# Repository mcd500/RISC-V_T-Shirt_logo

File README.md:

# RISC-V T-Shirt logo

Data files for RISC-V Ambassador logos used for creating T-Shirts and notebooks.

The first project used KiCad for designing T-Shirt logos.

The logo data is inspired by PCB layout of the real RISC-V board developed by SparkFun.

The T-Shirt.

## RISC-V Logs in Light Blue and Light Yellows.

## RISC-V Logs in Blue and Yellows.

## RISC-V Logs in Green and Pink.

## RISC-V Logs in Red and Green.

## RISC-V Ambassador logo data

Transparent background.

White background.

# Directory of all data.

## All image files

All image files are located under `images`.

[images](images/)

## Directory of KiCad data files.

The KiCad data was created by converting from original Eagle file format.

The project files and others of KiCad are located under ` SparkFun_REDV_RedBoard-kicad-logo-1`.

Links to the kicad data files.

[kicad](SparkFun_REDV_RedBoard-kicad-logo-1)

## Link to the SparkFun RED-V RedBoard.

https://www.sparkfun.com/products/15594

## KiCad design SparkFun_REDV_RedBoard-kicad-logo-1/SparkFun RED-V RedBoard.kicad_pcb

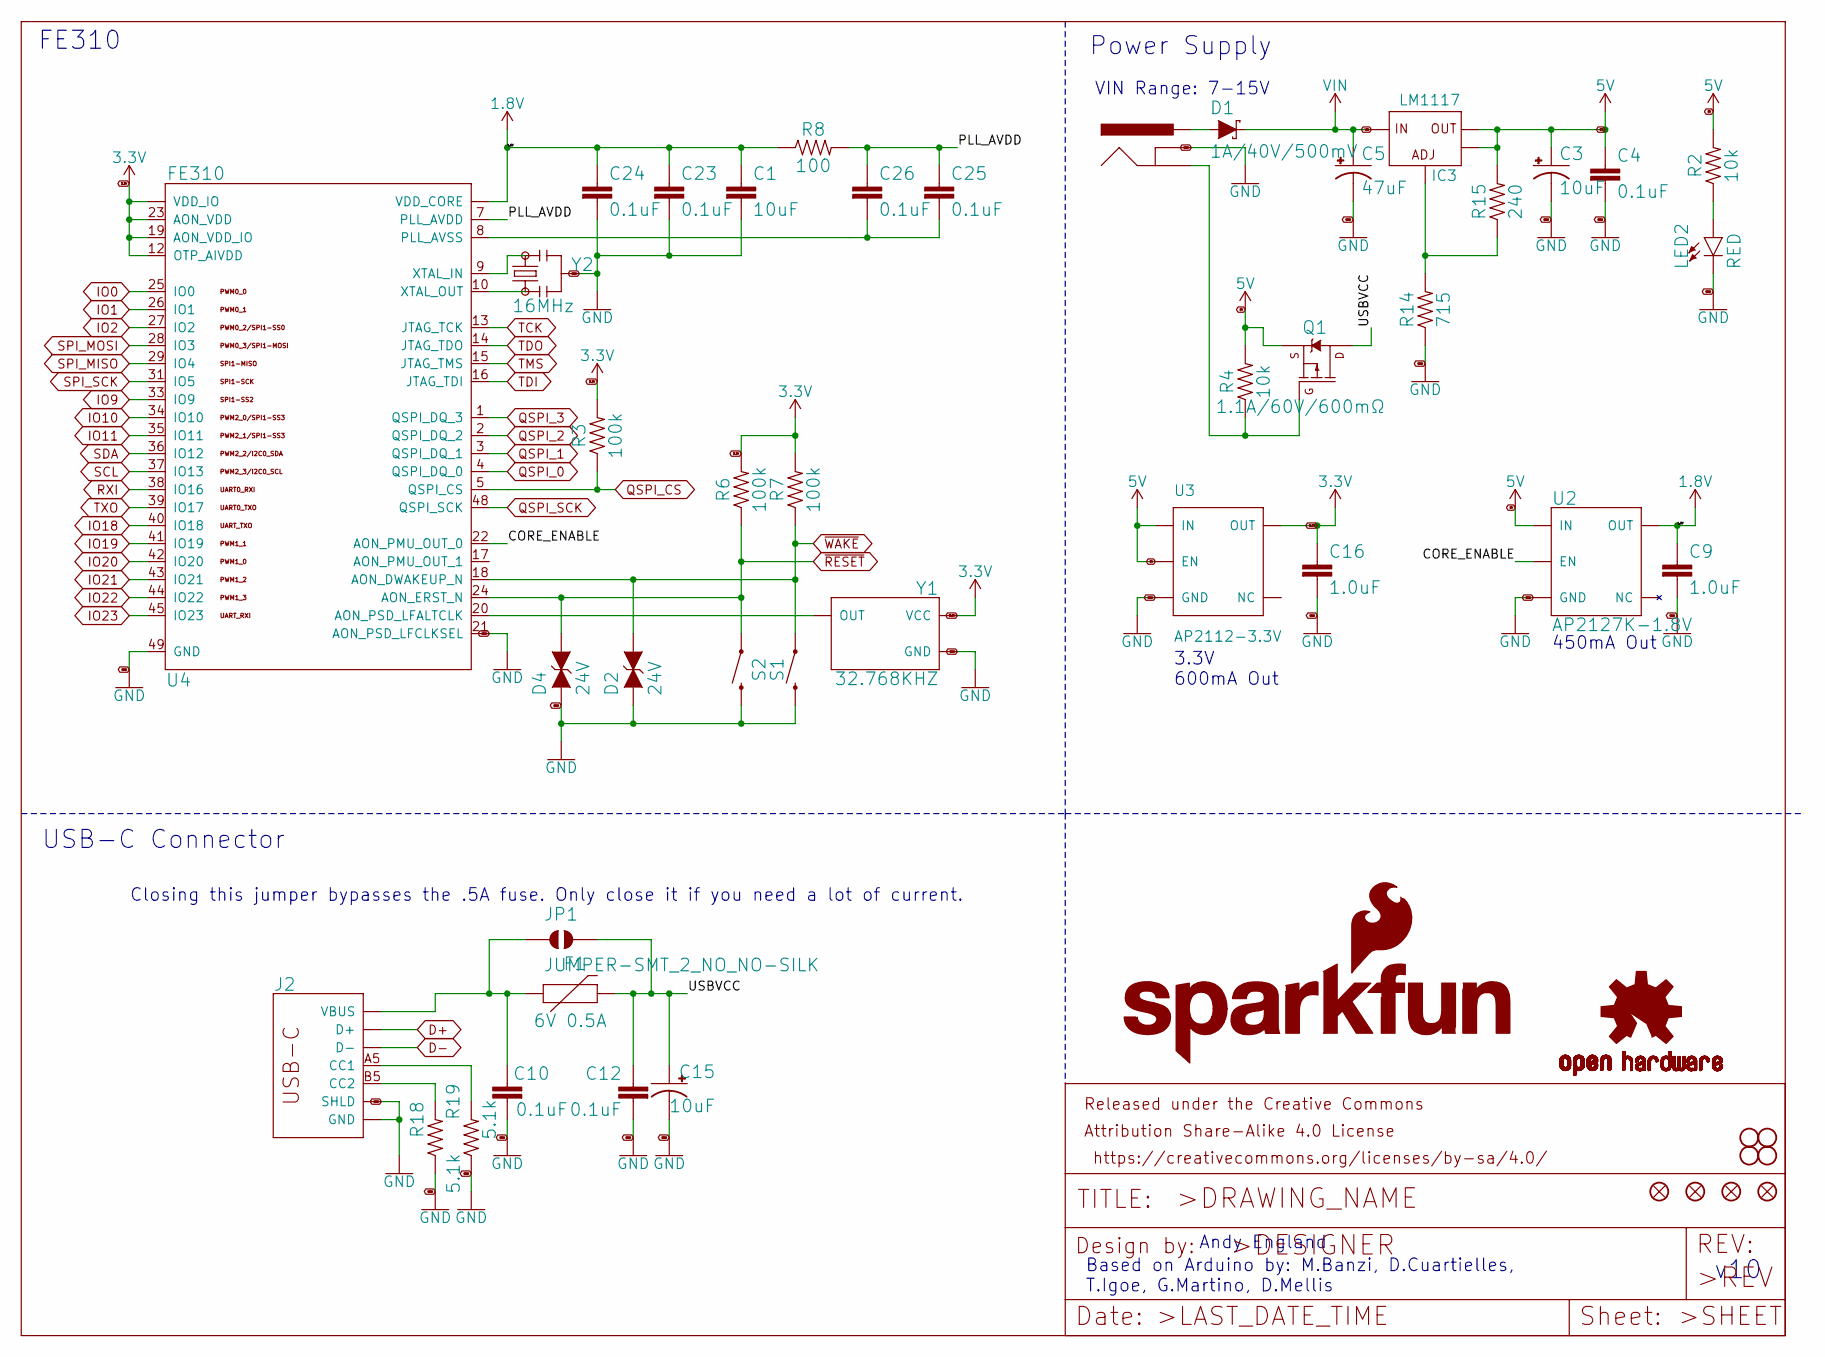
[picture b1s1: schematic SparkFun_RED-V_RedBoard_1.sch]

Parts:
C1: 10uF; 0603
C3, C15: 10uF; EIA3216
C4, C10, C12, C23, C24, C25, C26: 0.1uF; 0603
C5: 47uF; PANASONIC_D
C9, C16: 1.0uF; 0603
D1: 1A/40V/500mV; SMA-DIODE
D2, D4: 24V; 0603
F1: 6V 0.5A; 0805
FRAME2: FRAME-LETTER; CREATIVE_COMMONS
IC3: LM1117; SOT223-ALT1
J2: USB Female Type C Connector; USB-C-16P
J3: POWER_JACKSUPER_BOMB_DIGITY; POWER_JACK_SMD_OVERPASTE_SUPER_BOMB_DIGITY
JP1: JUMPER-SMT_2_NO_NO-SILK; SMT-JUMPER_2_NO_NO-SILK
JP3, JP4, JP5, JP6: STAND-OFF
JP8, JP9, JP15, JP16: FIDUCIAL1X2; FIDUCIAL-1X2
LED2: RED; LED-1206
LOGO1: SFE_LOGO_NAME_FLAME.1_INCH; SFE_LOGO_NAME_FLAME_.1
Q1: 1.1A/60V/600mΩ; SOT23-3
R2, R4: 10k; 0603
R3, R6, R7: 100k; 0603
R8: 100; 0603
R14: 715; 0603
R15: 240; 0603
R18, R19: 5.1k; 0603
S1, S2: MOMENTARY-SWITCH-SPST-SMD-6.2MM-TALL; TACTILE_SWITCH_SMD_6.2MM_TALL
U2: AP2127K-1.8V; SOT23-5
U3: AP2112-3.3V; SOT23-5
U4: FE310; QFN-48-.4MMPITCH
U$16: OSHW-LOGOS; OSHW-LOGO-S
Y1: 32.768KHZ; CRYSTAL-SMD-2X1.2MM
Y2: 16MHz; RESONATOR-SMD-3.2X1.3

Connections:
1.8V: C1.1, C9.1, C23.1, C24.1, R8.1, U2.5 (OUT), U4.6 (VDD_CORE), U4.30 (VDD_CORE), U4.46 (VDD_CORE)
3.3V: C16.1, R3.2, R6.2, R7.2, U3.5 (OUT), U4.11 (VDD_IO), U4.12 (OTP_AIVDD), U4.19 (AON_VDD_IO), U4.23 (AON_VDD), U4.32 (VDD_IO), U4.47 (VDD_IO), Y1.4 (VCC); also elsewhere on the board
5V: C3.+, C4.1, IC3.2 (OUT), IC3.4 (OUT@1), Q1.2 (S), R2.2, R4.2, R15.2, U2.1 (IN), U3.1 (IN), U3.3 (EN); also elsewhere on the board
/SparkFun RED-V RedBoard_1/CORE_ENABLE: U2.3 (EN), U4.22 (AON_PMU_OUT_0)
/SparkFun RED-V RedBoard_1/PLL_AVDD: C25.1, C26.1, R8.2, U4.7 (PLL_AVDD)
/SparkFun RED-V RedBoard_1/USBVCC: C12.1, C15.+, F1.2, JP1.2, Q1.3 (D)
D+: J2.A6 (D+), J2.B6 (D+); also elsewhere on the board
D-: J2.A7 (D-), J2.B7 (D-); also elsewhere on the board
GND: C1.2, C3.-, C4.2, C5.-, C9.2, C10.2, C12.2, C15.-, C16.2, C23.2, C24.2, D2.1 (A), D4.1 (A), J2.GND, J2.GND2 (GND), J2.SHLD1 (SHLD), J2.SHLD2 (SHLD), J2.SHLD3 (SHLD), J2.SHLD4 (SHLD), J2.SHLD5 (SHLD), J2.SHLD6 (SHLD), J2.SHLD7 (SHLD), J2.SHLD8 (SHLD), J3.GND (GNDBREAK), LED2.C, R14.1, R18.1, R19.1, S1.B2 (2), S2.B2 (2), U2.2 (GND), U3.2 (GND), U4.21 (AON_PSD_LFCLKSEL), U4.49 (GND), Y1.2 (GND), Y2.2; also elsewhere on the board
IO0: U4.25 (IO0); also elsewhere on the board
IO1: U4.26 (IO1); also elsewhere on the board
IO2: U4.27 (IO2); also elsewhere on the board
IO9: U4.33 (IO9); also elsewhere on the board
IO10: U4.34 (IO10); also elsewhere on the board
IO11: U4.35 (IO11); also elsewhere on the board
IO18: U4.40 (IO18); also elsewhere on the board
IO19: U4.41 (IO19); also elsewhere on the board
IO20: U4.42 (IO20); also elsewhere on the board
IO21: U4.43 (IO21); also elsewhere on the board
IO22: U4.44 (IO22); also elsewhere on the board
IO23: U4.45 (IO23); also elsewhere on the board
unnamed: C10.1, F1.1, J2.VBUS1 (VBUS), J2.VBUS2 (VBUS), JP1.1
unnamed: C25.2, C26.2, U4.8 (PLL_AVSS)
unnamed: D1.A, J3.VIN0 (PWR)
unnamed: IC3.1 (ADJ), R14.2, R15.1
unnamed: J2.A5 (CC1), R19.2
unnamed: J2.B5 (CC2), R18.2
unnamed: J3.P$4 (GND), Q1.1 (G), R4.1
unnamed: LED2.A, R2.1
unnamed: U4.9 (XTAL_IN), Y2.3
unnamed: U4.10 (XTAL_OUT), Y2.1
unnamed: U4.20 (AON_PSD_LFALTCLK), Y1.3 (OUT)
QSPI_0: U4.4 (QSPI_DQ_0); also elsewhere on the board
QSPI_1: U4.3 (QSPI_DQ_1); also elsewhere on the board
QSPI_2: U4.2 (QSPI_DQ_2); also elsewhere on the board
QSPI_3: U4.1 (QSPI_DQ_3); also elsewhere on the board
QSPI_CS: R3.1, U4.5 (QSPI_CS); also elsewhere on the board
QSPI_SCK: U4.48 (QSPI_SCK); also elsewhere on the board
RXI: U4.38 (IO16); also elsewhere on the board
SCL: U4.37 (IO13); also elsewhere on the board
SDA: U4.36 (IO12); also elsewhere on the board
SPI_MISO: U4.29 (IO4); also elsewhere on the board
SPI_MOSI: U4.28 (IO3); also elsewhere on the board
SPI_SCK: U4.31 (IO5); also elsewhere on the board
TCK: U4.13 (JTAG_TCK); also elsewhere on the board
TDI: U4.16 (JTAG_TDI); also elsewhere on the board
TDO: U4.14 (JTAG_TDO); also elsewhere on the board
TMS: U4.15 (JTAG_TMS); also elsewhere on the board
TXO: U4.39 (IO17); also elsewhere on the board
VIN: C5.+, D1.C, IC3.3 (IN); also elsewhere on the board
~RESET: D4.2 (C), R6.1, S2.A2 (1), U4.24 (AON_ERST_N); also elsewhere on the board
~WAKE: D2.2 (C), R7.1, S1.A2 (1), U4.18 (AON_DWAKEUP_N); also elsewhere on the board

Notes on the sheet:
Power Supply
FE310
USB-C Connector
Based on Arduino by: M.Banzi, D.Cuartielles, T.Igoe, G.Martino, D.Mellis
Andy England
v10
VIN Range: 7-15V
3.3V 600mA Out
450mA Out
Closing this jumper bypasses the .5A fuse. Only close it if you need a lot of current.

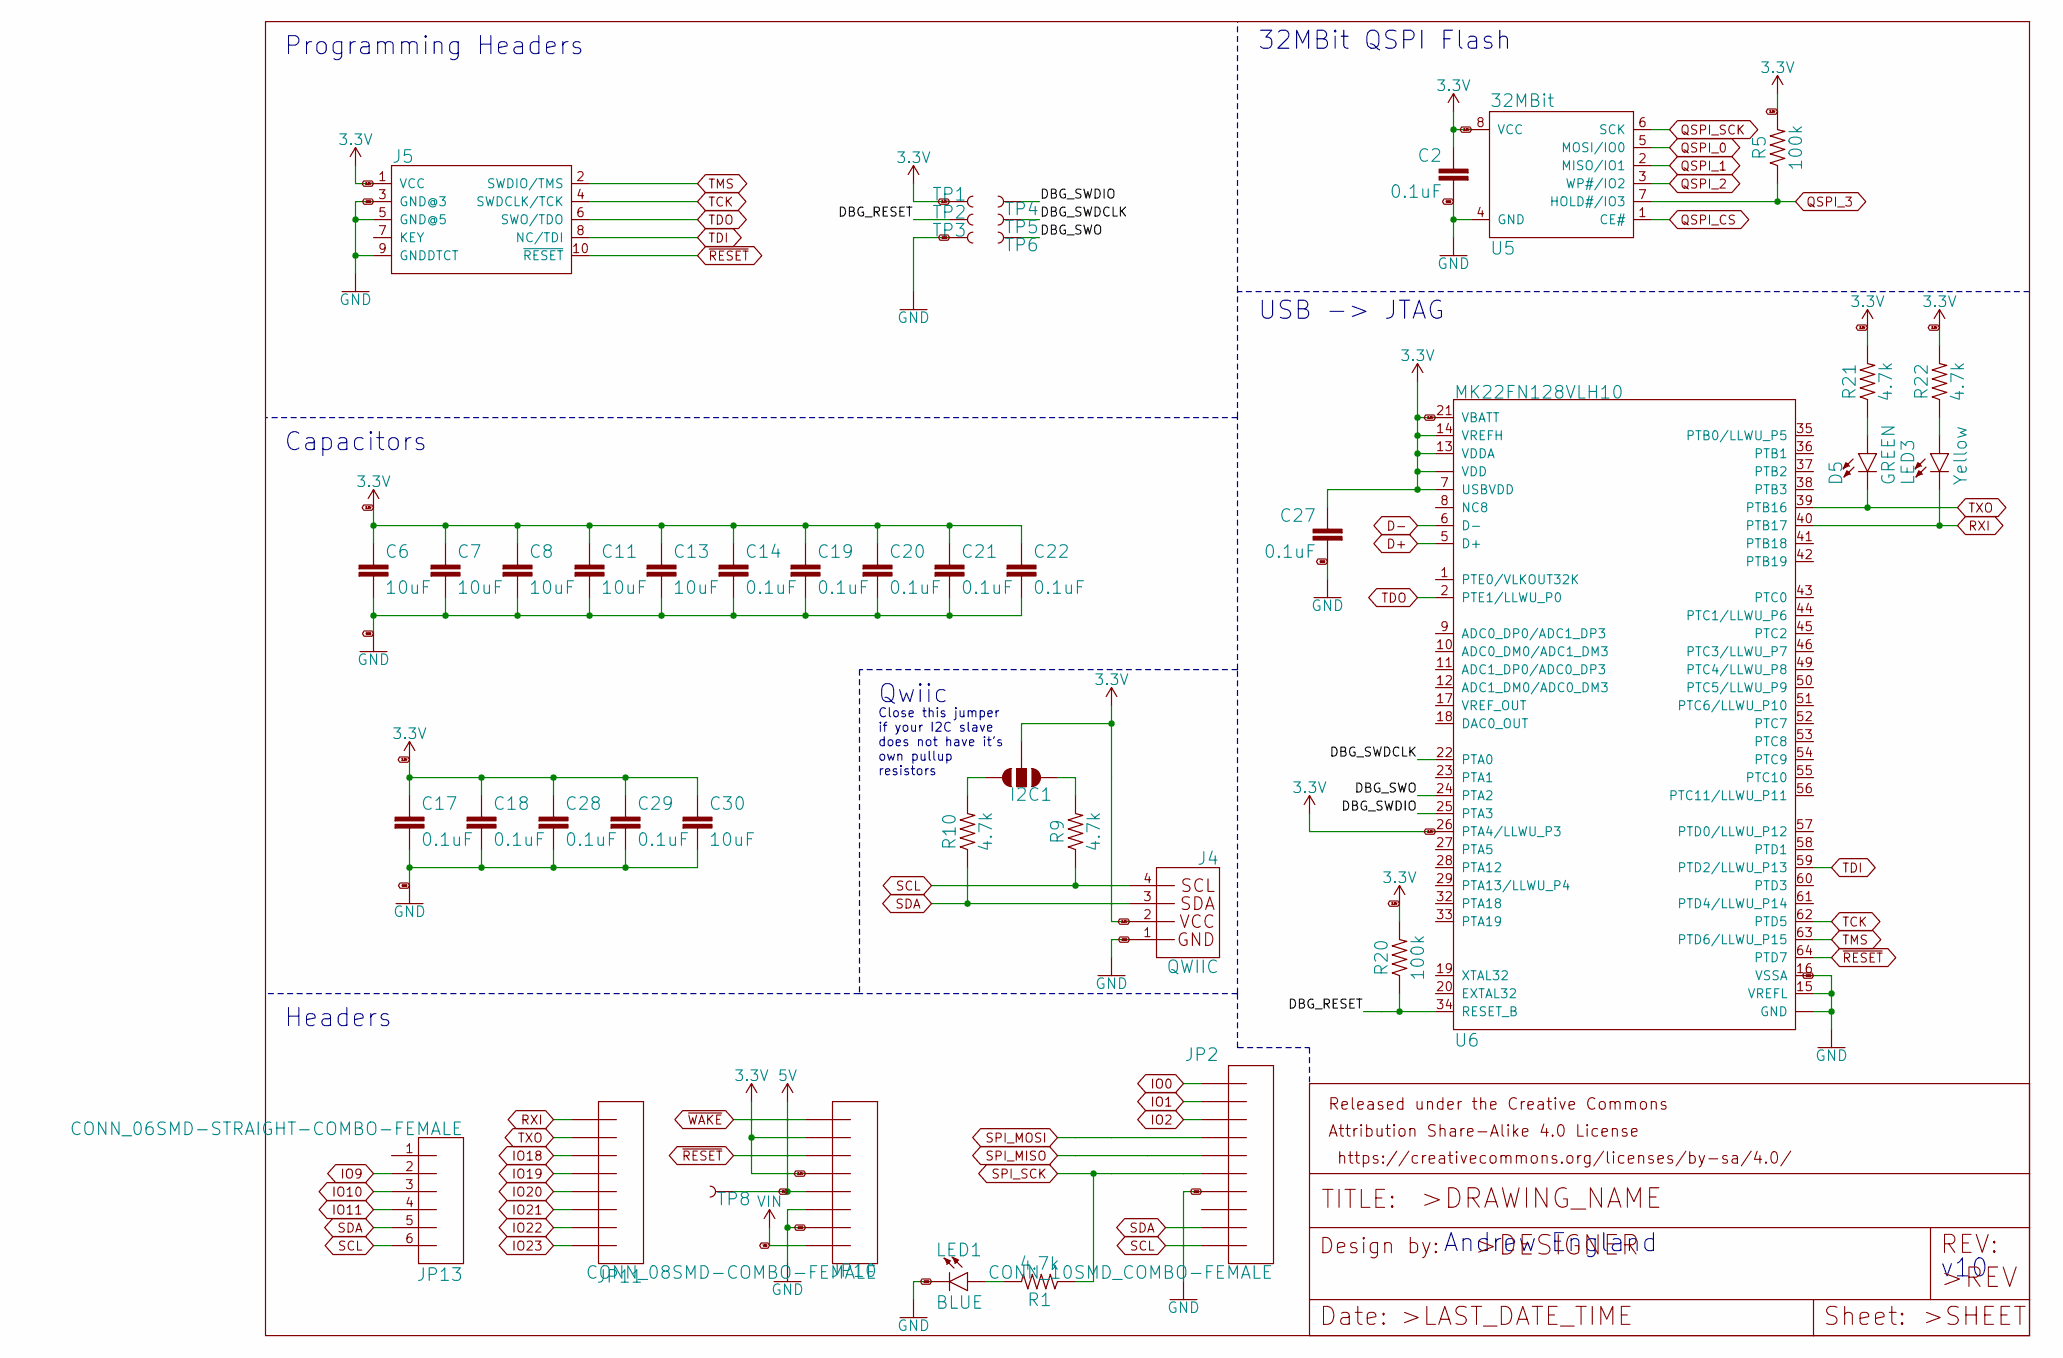
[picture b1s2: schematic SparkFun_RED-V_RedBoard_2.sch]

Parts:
C2, C14, C17, C18, C19, C20, C21, C22, C27, C28, C29: 0.1uF; 0603
C6, C7, C8, C11, C13, C30: 10uF; 0603
D5: GREEN; LED-1206
FRAME1: FRAME-LETTER; CREATIVE_COMMONS
I2C: JUMPER-SMT_3_NO_NO-SILK; SMT-JUMPER_3_NO_NO-SILK
J4: QWIIC; JST04_1MM_RA
J5: CORTEX_JTAG_DEBUG_PTH_NS; 2X5-PTH-1.27MM-NO_SILK
JP2: CONN_10SMD_COMBO-FEMALE; 1X10_SMD_COMBINED
JP10: CONN_08SMD-COMBO-FEMALE; 1X08_SMD_COMBINED
JP11: JP11; 1X08_SMD_COMBINED
JP13: CONN_06SMD-STRAIGHT-COMBO-FEMALE; 1X06_SMD_STRAIGHT_COMBO
LED1: BLUE; LED-1206
LED3: Yellow; LED-1206
R1, R9, R10, R21, R22: 4.7k; 0603
R5, R20: 100k; 0603
TP1, TP2, TP3, TP4, TP5, TP6: TEST-POINT3X5; PAD.03X.05
TP8: TEST-POINT3; PAD.03X.03
U5: 32MBit; SO08
U6: MK22FN128VLH10; LQFP-64

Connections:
3.3V: C2.1, C6.1, C7.1, C8.1, C11.1, C13.1, C14.1, C17.1, C18.1, C19.1, C20.1, C21.1, C22.1, C27.1, C28.1, C29.1, C30.1, J4.2, J5.1 (VCC), JP10.5, JP10.5@2 (5), JP10.7, JP10.7@2 (7), R5.2, R20.2, R21.2, R22.2, TP1.P$1, U5.8 (VCC), U6.3 (VDD), U6.7 (USBVDD), U6.13 (VDDA), U6.14 (VREFH), U6.21 (VBATT), U6.26 (PTA4/LLWU_P3), U6.30 (VDD), U6.48 (VDD); also elsewhere on the board
5V: JP10.4, JP10.4@2 (4), TP8.P$1; also elsewhere on the board
/SparkFun RED-V RedBoard_2/DBG_RESET: R20.1, TP2.P$1, U6.34 (RESET_B)
/SparkFun RED-V RedBoard_2/DBG_SWDCLK: TP5.P$1, U6.22 (PTA0)
/SparkFun RED-V RedBoard_2/DBG_SWDIO: TP4.P$1, U6.25 (PTA3)
/SparkFun RED-V RedBoard_2/DBG_SWO: TP6.P$1, U6.24 (PTA2)
D+: U6.5 (D+); also elsewhere on the board
D-: U6.6 (D-); also elsewhere on the board
GND: C2.2, C6.2, C7.2, C8.2, C11.2, C13.2, C14.2, C17.2, C18.2, C19.2, C20.2, C21.2, C22.2, C27.2, C28.2, C29.2, C30.2, J4.1, J5.3 (GND@3), J5.5 (GND@5), J5.9 (GNDDTCT), JP2.4A (4), JP2.4B (4), JP10.2, JP10.2@2 (2), JP10.3, JP10.3@2 (3), LED1.C, TP3.P$1, U5.4 (GND), U6.4 (GND), U6.15 (VREFL), U6.16 (VSSA), U6.31 (GND), U6.47 (GND); also elsewhere on the board
IO0: JP2.10A (10), JP2.10B (10); also elsewhere on the board
IO1: JP2.9A (9), JP2.9B (9); also elsewhere on the board
IO2: JP2.8A (8), JP2.8B (8); also elsewhere on the board
IO9: JP13.2; also elsewhere on the board
IO10: JP13.3; also elsewhere on the board
IO11: JP13.4; also elsewhere on the board
IO18: JP11.3, JP11.3@2 (3); also elsewhere on the board
IO19: JP11.4, JP11.4@2 (4); also elsewhere on the board
IO20: JP11.5, JP11.5@2 (5); also elsewhere on the board
IO21: JP11.6, JP11.6@2 (6); also elsewhere on the board
IO22: JP11.7, JP11.7@2 (7); also elsewhere on the board
IO23: JP11.8, JP11.8@2 (8); also elsewhere on the board
unnamed: D5.A, R21.1
unnamed 29: R9.2; also elsewhere on the board
unnamed 30: R10.2; also elsewhere on the board
unnamed: JP2.3A (3), JP2.3B (3)
unnamed: LED1.A, R1.2
unnamed: LED3.A, R22.1
QSPI_0: U5.5 (MOSI/IO0); also elsewhere on the board
QSPI_1: U5.2 (MISO/IO1); also elsewhere on the board
QSPI_2: U5.3 (WP#/IO2); also elsewhere on the board
QSPI_3: R5.1, U5.7 (HOLD#/IO3); also elsewhere on the board
QSPI_CS: U5.1 (CE#); also elsewhere on the board
QSPI_SCK: U5.6 (SCK); also elsewhere on the board
RXI: JP11.1, JP11.1@2 (1), LED3.C, U6.40 (PTB17); also elsewhere on the board
SCL: J4.4, JP2.1A (1), JP2.1B (1), JP13.6, R9.1; also elsewhere on the board
SDA: J4.3, JP2.2A (2), JP2.2B (2), JP13.5, R10.1; also elsewhere on the board
SPI_MISO: JP2.6A (6), JP2.6B (6); also elsewhere on the board
SPI_MOSI: JP2.7A (7), JP2.7B (7); also elsewhere on the board
SPI_SCK: JP2.5A (5), JP2.5B (5), R1.1; also elsewhere on the board
TCK: J5.4 (SWDCLK/TCK), U6.62 (PTD5); also elsewhere on the board
TDI: J5.8 (NC/TDI), U6.59 (PTD2/LLWU_P13); also elsewhere on the board
TDO: J5.6 (SWO/TDO), U6.2 (PTE1/LLWU_P0); also elsewhere on the board
TMS: J5.2 (SWDIO/TMS), U6.63 (PTD6/LLWU_P15); also elsewhere on the board
TXO: D5.C, JP11.2, JP11.2@2 (2), U6.39 (PTB16); also elsewhere on the board
VIN: JP10.1, JP10.1@2 (1); also elsewhere on the board
~RESET: J5.10 (~RESET), JP10.6, JP10.6@2 (6), U6.64 (PTD7); also elsewhere on the board
~WAKE: JP10.8, JP10.8@2 (8); also elsewhere on the board

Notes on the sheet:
Qwiic
Headers
Programming Headers
32MBit QSPI Flash
Capacitors
Andrew England
v10
USB -> JTAG
Close this jumper if your I2C slave does not have it's own pullup resistors

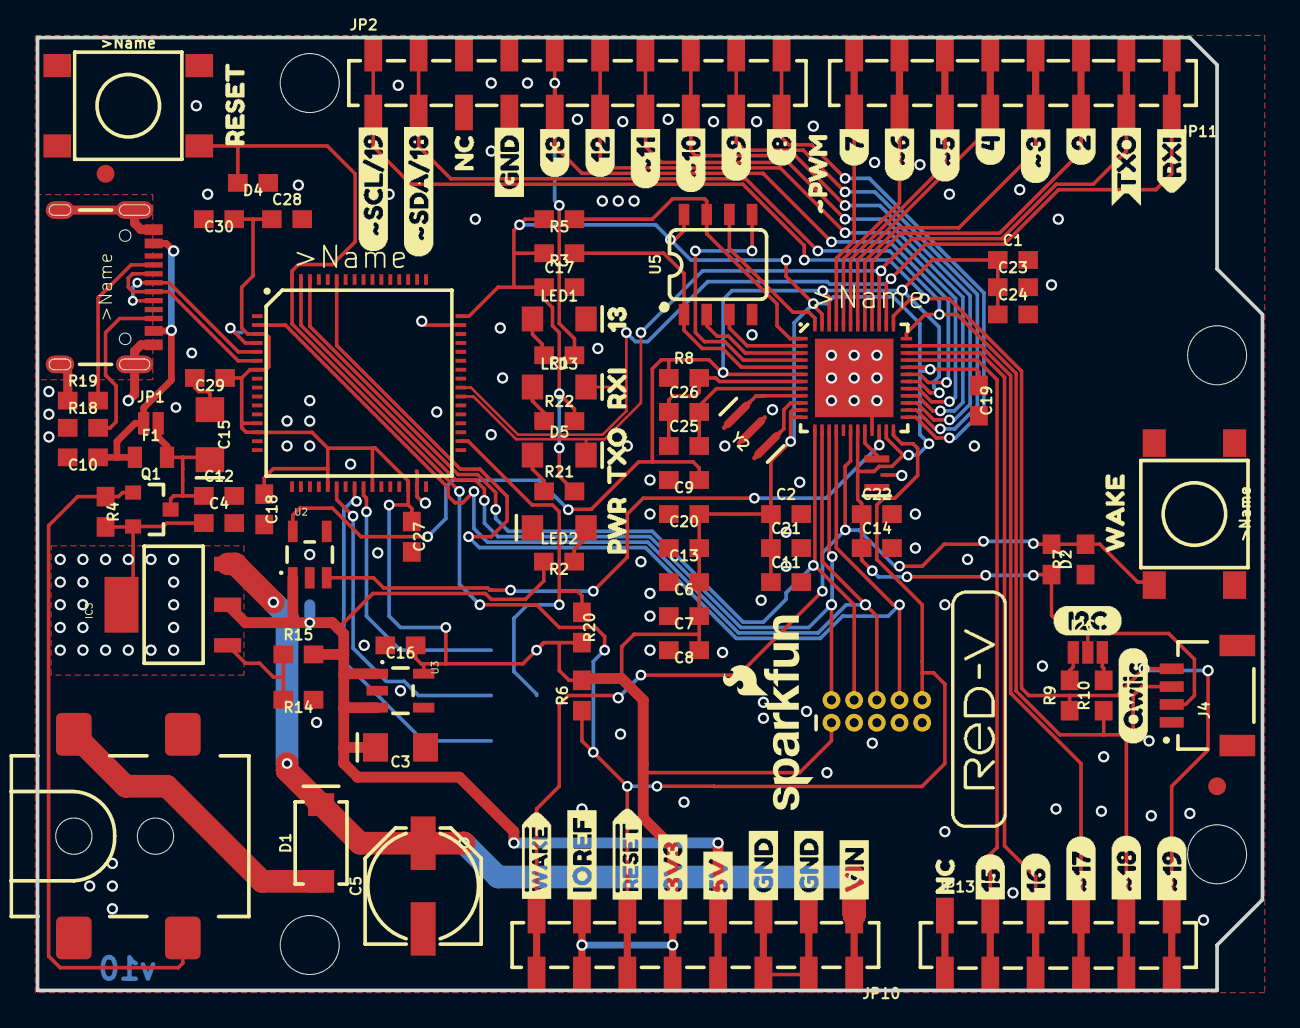
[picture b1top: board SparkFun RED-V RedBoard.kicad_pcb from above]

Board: 2 copper layers, 68.6 x 53.3 mm, 138 parts (0 on the bottom side), 62 nets.

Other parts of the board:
I2C1: JUMPER-SMT_3_NO_NO-SILK; SMT-JUMPER_3_NO_NO-SILK
U$1: (QWIIC)
U$2: #324
U$3: #522
U$4: #621
U$8: SEGGERLOGO#PNG
U$9: #918
U$11: I2C0
U$14: #1017
U$15: #1116
U$17: #1710
U$18: #1812
U$19: #1911
U$20: #RESET2
U$21: #SCL#1926
U$22: #SDA#1827
U$23: #WAKE0
U$24: 3V33
U$25: 5V4
U$26: 158
U$27: 169
U$28: 225
U$29: 423
U$30: 720
U$31: 819
U$32: 1215
U$33: 1314
U$34, U$35, U$36: GND5
U$37: IOREF1
U$38, U$43: NC7
U$39: RXI29
U$40: TXO28
U$41: VIN6
U$42: _#PWM30
U$45: 133
U$46: PWR0
U$47: RXI1
U$48: TXO2
U$49: RESET0
U$50: WAKE1
U$52: REDFIVE_LOGO#05#PNG

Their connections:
3.3V: I2C1.2; also elsewhere on the board
unnamed 29: I2C1.1; also elsewhere on the board
unnamed 30: I2C1.3; also elsewhere on the board

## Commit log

2023-04-05 Add README
2023-04-05 Add kicad data used for creating RISC-V logos
2023-04-05 Add RISC-V logo image files when making RISC-V T Shirts
2023-04-05 Adding links to images in README
2023-04-05 Fixing markdown sytax
2023-04-05 Add T-shirt image
2023-04-05 Fix typo
2023-04-05 Typo
2023-04-05 Typo and adding section name

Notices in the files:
parts and their libraries:
https://creativecommons.org/licenses/by-sa/4.0
Released under the Creative Commons Attribution Share-Alike 4.0 License
